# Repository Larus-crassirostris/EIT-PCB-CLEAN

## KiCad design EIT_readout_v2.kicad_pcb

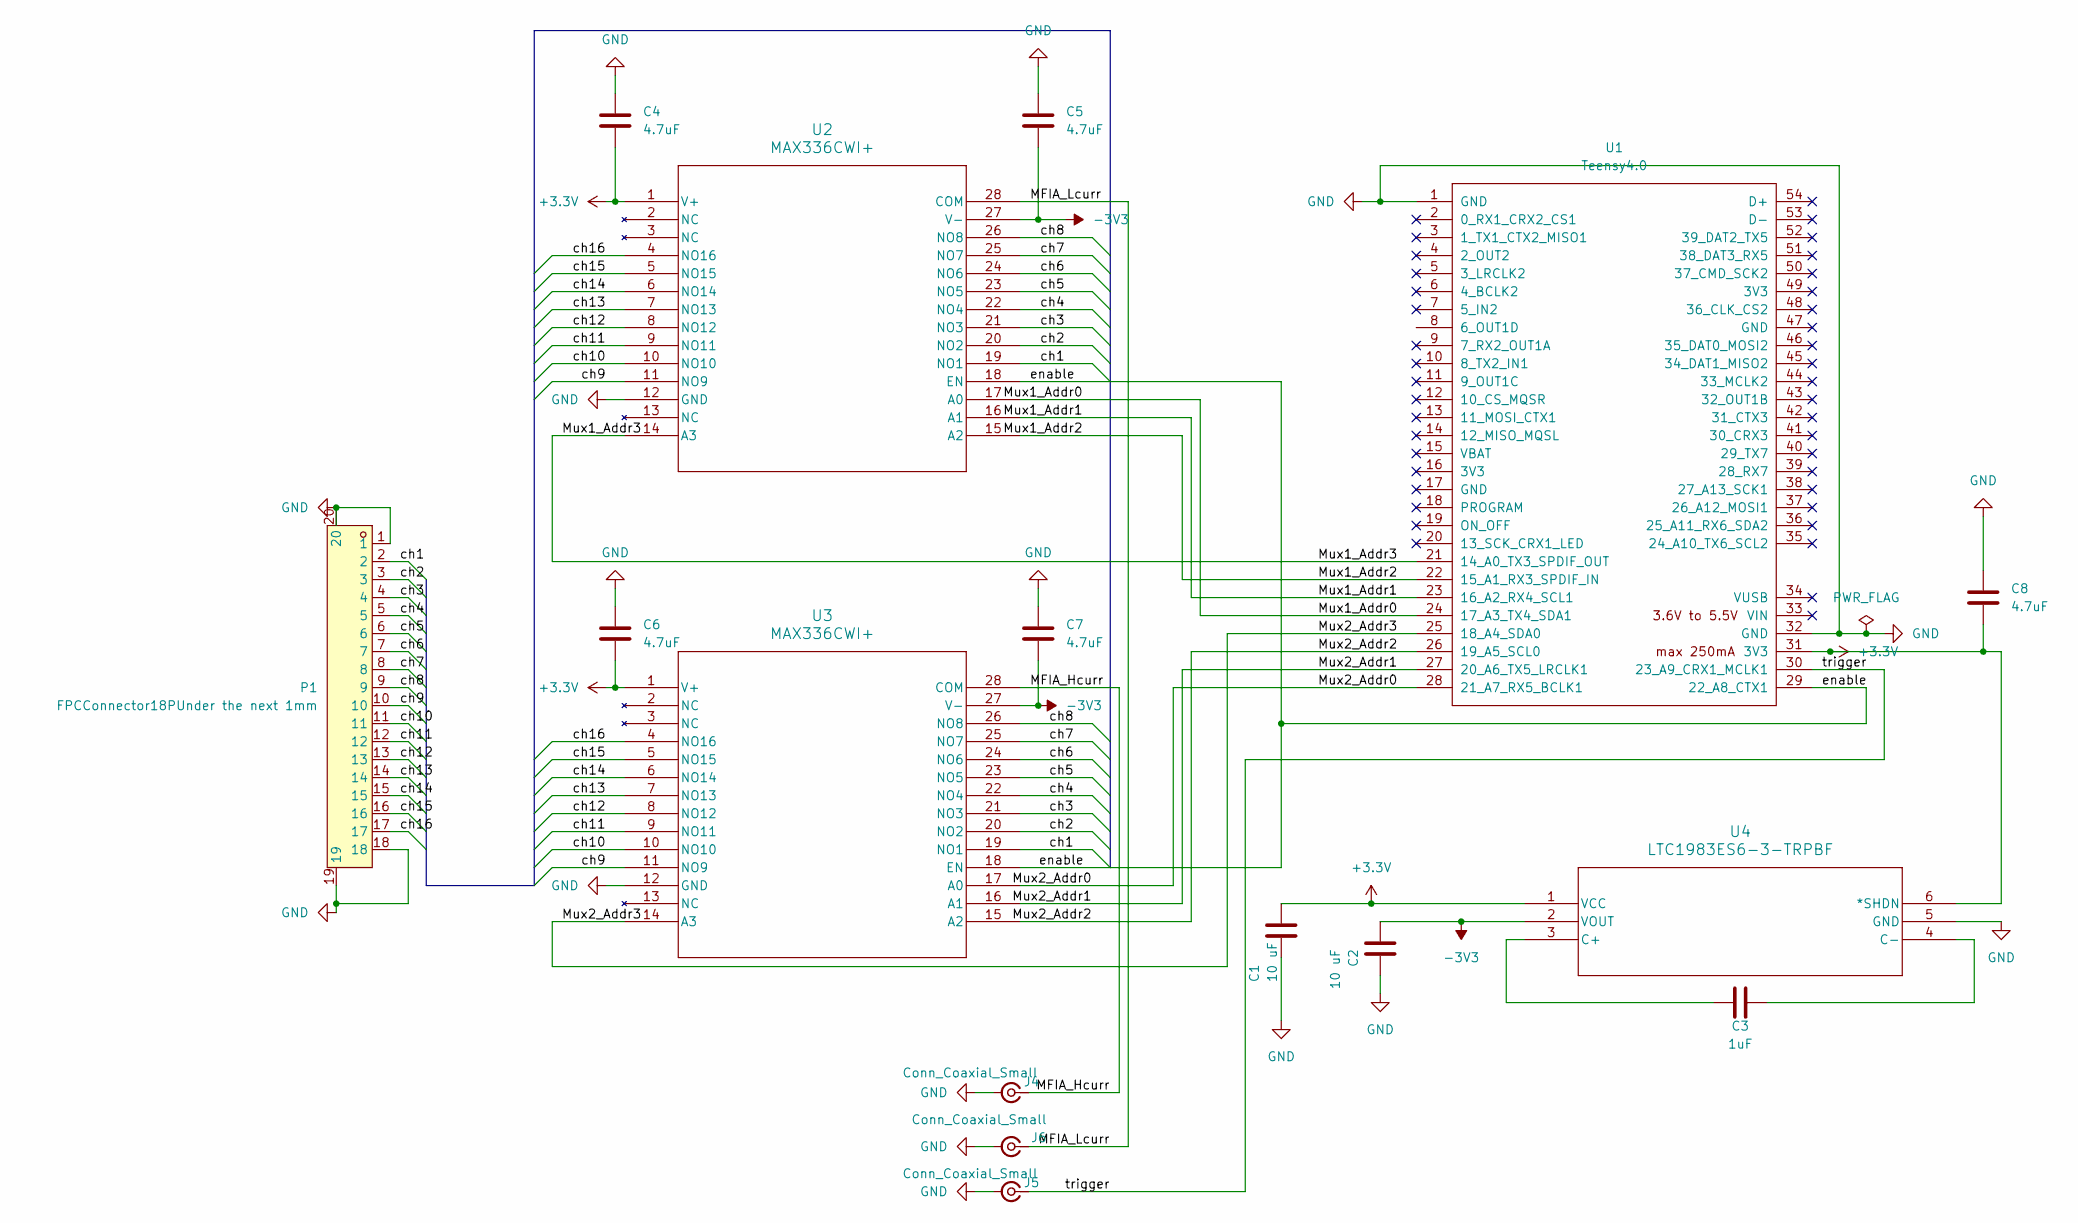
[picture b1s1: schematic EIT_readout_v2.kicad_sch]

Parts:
C1, C2: 10 uF; C_1206_3216Metric_Pad1.33x1.80mm_HandSolder
C3: 1uF; C_1206_3216Metric_Pad1.33x1.80mm_HandSolder
C4, C5, C6, C7, C8: 4.7uF; C0603
J4, J5, J6: Conn_Coaxial_Small; SMA_Molex_73251-1153_EdgeMount_Horizontal
P1: FPCConnector18PUnder the next 1mm; FPC-SMD_18P-P1.00_AFA07-S18FCC-00; MPN AFA07-S18FCC-00; LCSC Part C23826
U1: Teensy4.0; Teensy40_SMT
U2, U3: MAX336CWI+; 21-0042B_28_MXM
U4: LTC1983ES6-3-TRPBF; SOT-23_S6_LIT

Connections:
+3.3V: C1.1, C4.2, C6.2, C8.2, U1.31 (3V3), U2.1 (V+), U3.1 (V+), U4.1 (VCC), U4.6 (*SHDN)
-3V3: C2.2, C5.2, C7.2, U2.27 (V-), U3.27 (V-), U4.2 (VOUT)
/MFIA_Hcurr: J4.1 (In), U3.28 (COM)
/MFIA_Lcurr: J6.1 (In), U2.28 (COM)
/Mux1_Addr0: U1.24 (17_A3_TX4_SDA1), U2.17 (A0)
/Mux1_Addr1: U1.23 (16_A2_RX4_SCL1), U2.16 (A1)
/Mux1_Addr2: U1.22 (15_A1_RX3_SPDIF_IN), U2.15 (A2)
/Mux1_Addr3: U1.21 (14_A0_TX3_SPDIF_OUT), U2.14 (A3)
/Mux2_Addr0: U1.28 (21_A7_RX5_BCLK1), U3.17 (A0)
/Mux2_Addr1: U1.27 (20_A6_TX5_LRCLK1), U3.16 (A1)
/Mux2_Addr2: U1.26 (19_A5_SCL0), U3.15 (A2)
/Mux2_Addr3: U1.25 (18_A4_SDA0), U3.14 (A3)
/ch1: P1.2, U2.19 (NO1), U3.19 (NO1)
/ch2: P1.3, U2.20 (NO2), U3.20 (NO2)
/ch3: P1.4, U2.21 (NO3), U3.21 (NO3)
/ch4: P1.5, U2.22 (NO4), U3.22 (NO4)
/ch5: P1.6, U2.23 (NO5), U3.23 (NO5)
/ch6: P1.7, U2.24 (NO6), U3.24 (NO6)
/ch7: P1.8, U2.25 (NO7), U3.25 (NO7)
/ch8: P1.9, U2.26 (NO8), U3.26 (NO8)
/ch9: P1.10, U2.11 (NO9), U3.11 (NO9)
/ch10: P1.11, U2.10 (NO10), U3.10 (NO10)
/ch11: P1.12, U2.9 (NO11), U3.9 (NO11)
/ch12: P1.13, U2.8 (NO12), U3.8 (NO12)
/ch13: P1.14, U2.7 (NO13), U3.7 (NO13)
/ch14: P1.15, U2.6 (NO14), U3.6 (NO14)
/ch15: P1.16, U2.5 (NO15), U3.5 (NO15)
/ch16: P1.17, U2.4 (NO16), U3.4 (NO16)
/enable: U1.29 (22_A8_CTX1), U2.18 (EN), U3.18 (EN)
/trigger: J5.1 (In), U1.30 (23_A9_CRX1_MCLK1)
GND: C1.2, C2.1, C4.1, C5.1, C6.1, C7.1, C8.1, J4.2 (Ext), J5.2 (Ext), J6.2 (Ext), P1.1, P1.18, P1.19, P1.20, U1.1 (GND), U1.32 (GND), U2.12 (GND), U3.12 (GND), U4.5 (GND)
unnamed: C3.2, U4.3 (C+)
unnamed: C3.1, U4.4 (C-)

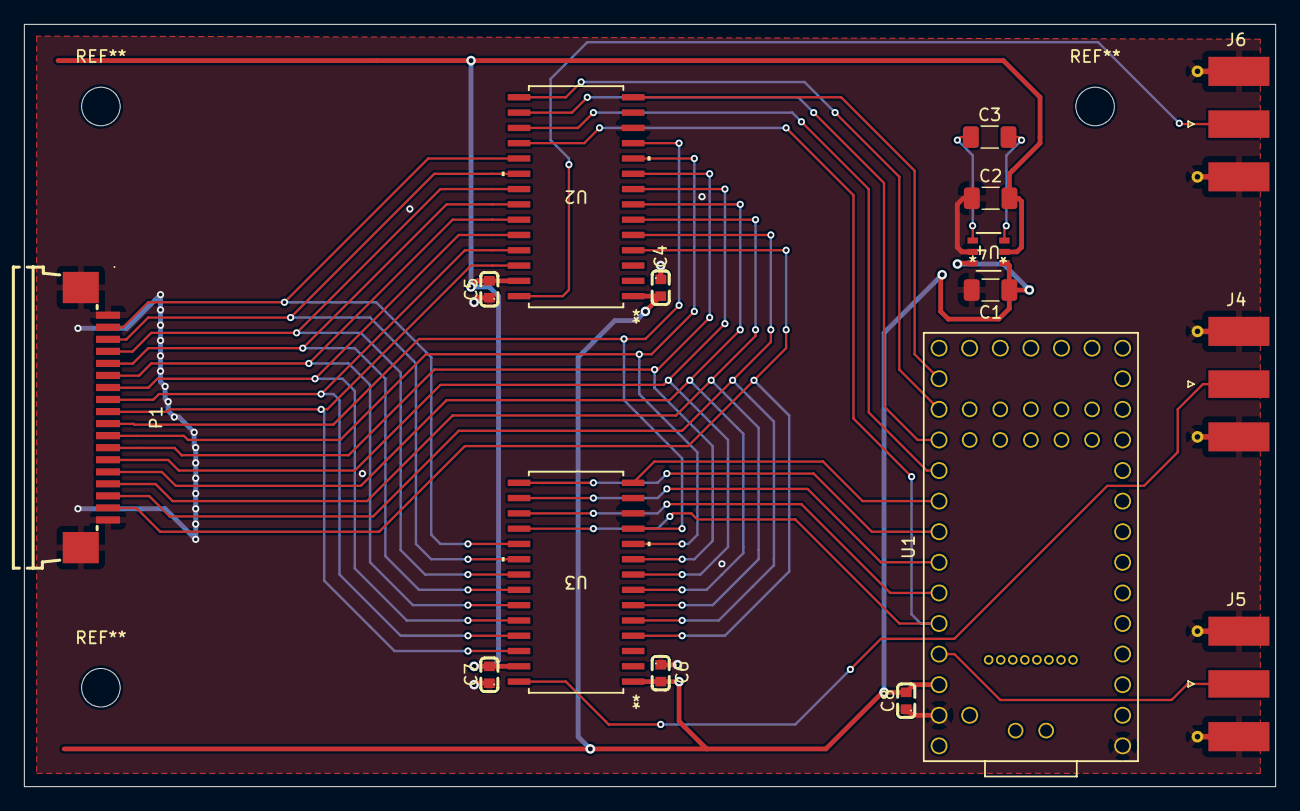
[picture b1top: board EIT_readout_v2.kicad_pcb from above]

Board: 2 copper layers, 103.9 x 63.3 mm, 16 parts (0 on the bottom side), 33 nets.

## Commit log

2026-06-04 Add .gitignore
2026-06-04 Add KiCad project files and teensy libraries
2026-06-04 added M3 Mounting holes to the PCB
2026-06-04 Added via to ground plane, also added footprint for MAX336 to library
2026-06-17 changed the readout PCB FPC holder to 18 pins to accommodate ground
